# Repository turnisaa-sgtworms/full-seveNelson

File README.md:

my fun little keeb: 

designed to fit in a 60% case (minus two of the mounting points)

7u main cluster with a southy num pad and arrow keys/mini nav cluster

stm32 powered

built with the help of this guide: https://youtu.be/kGKN8SGkUD0?si=LNXGM9T6t6xvs4m5
by noah kiser

plate files are added, but will need updated when i fix the spacing :(

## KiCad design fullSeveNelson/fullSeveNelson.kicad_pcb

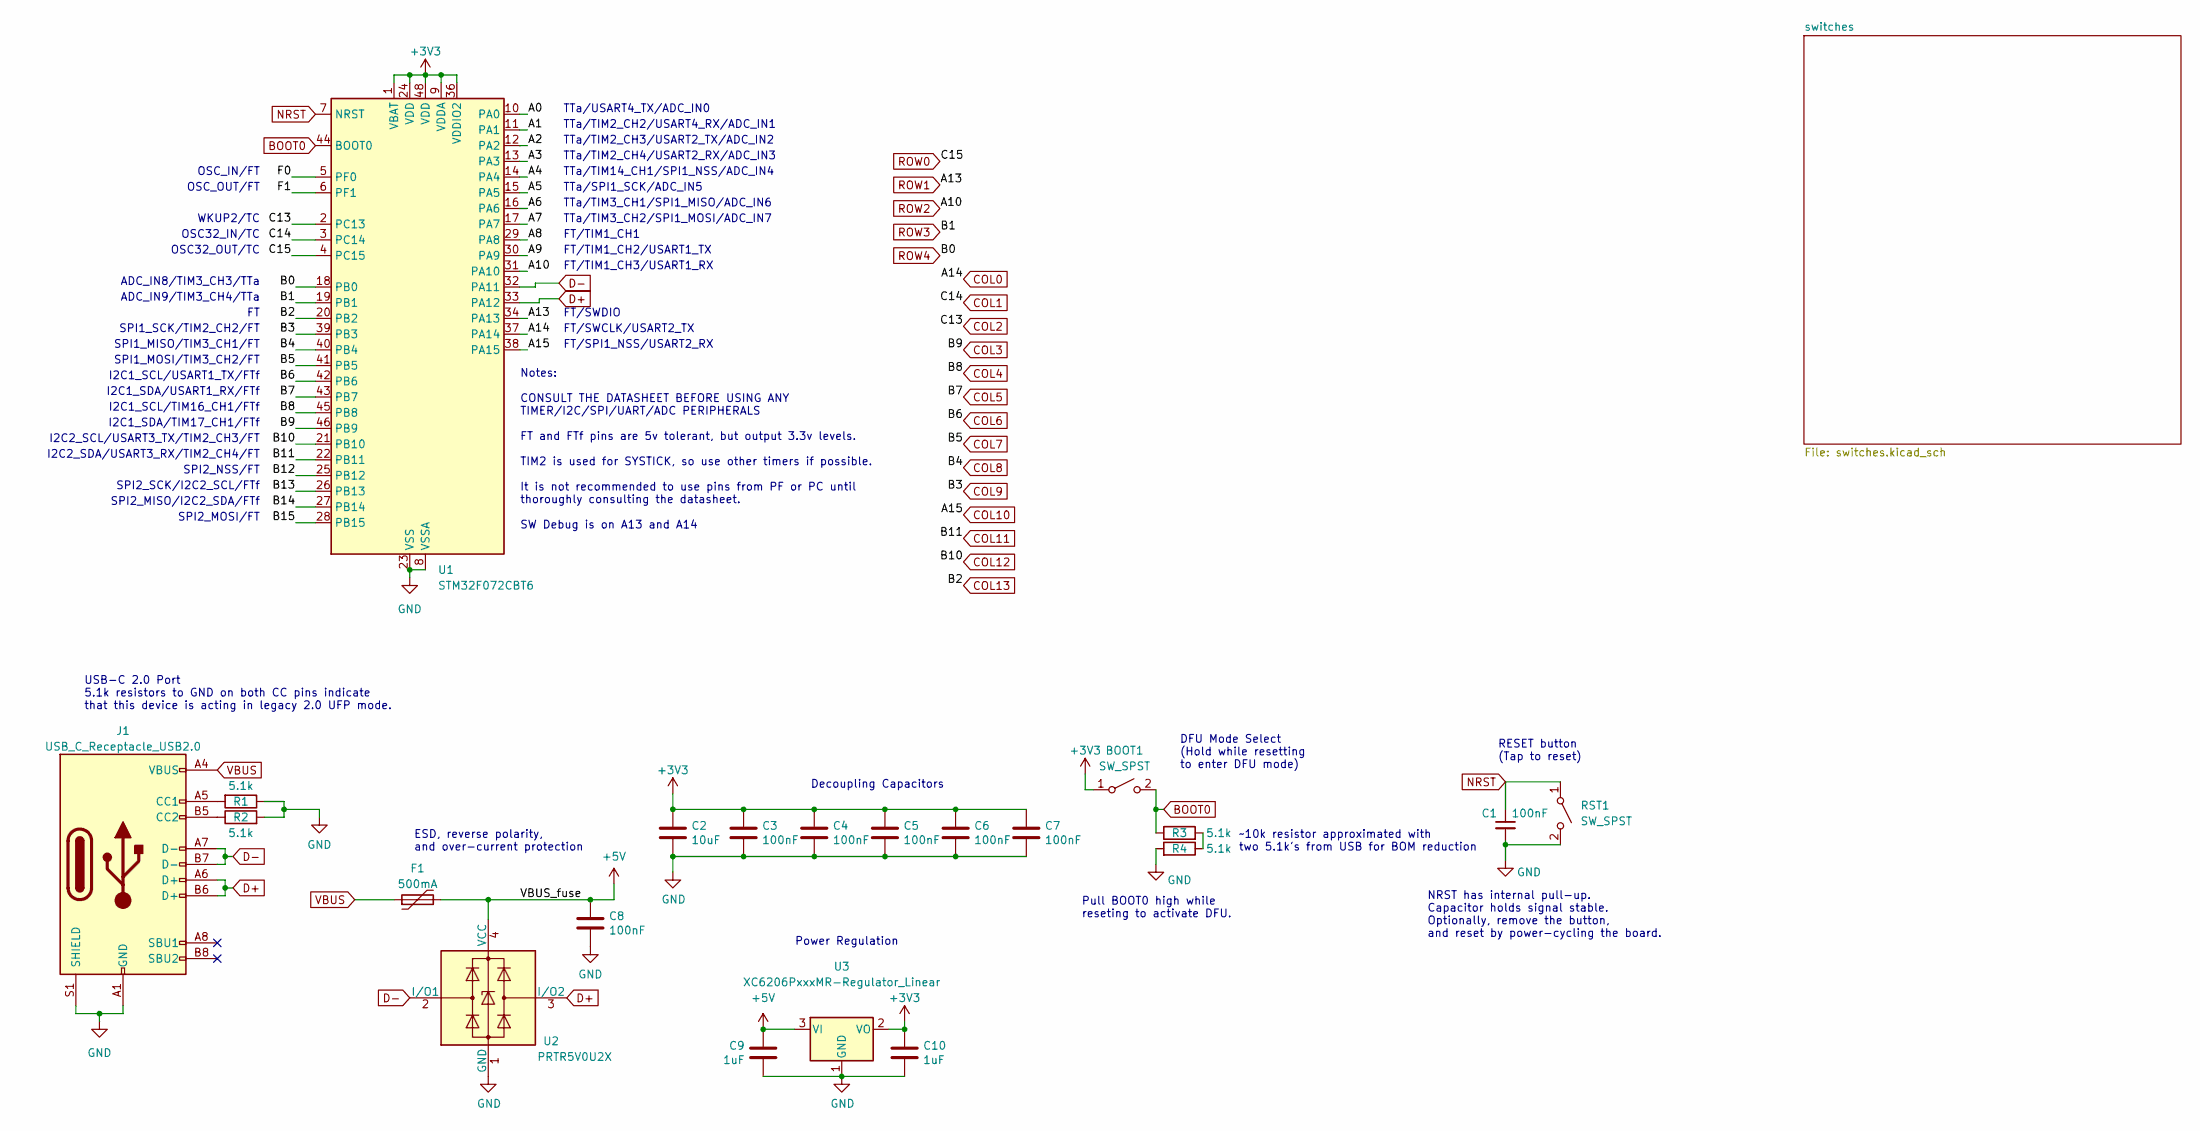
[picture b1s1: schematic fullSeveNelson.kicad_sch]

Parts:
BOOT1: SW_SPST; SW_SPST_TL3342
C1, C3, C4, C5, C6, C7, C8: 100nF; C_0402_1005Metric; LCSC C307331
C2: 10uF; C_0603_1608Metric; LCSC C307331
C9, C10: 1uF; C_0402_1005Metric; LCSC C307331
F1: 500mA; Fuse_1206_3216Metric; LCSC C135341
J1: USB_C_Receptacle_USB2.0; USB_C_Receptacle_HRO_TYPE-C-31-M-12; JlcRotOffset 180
R1, R2, R3, R4: 5.1k; R_0402_1005Metric
RST1: SW_SPST; SW_SPST_TL3342
U1: STM32F072CBT6; LQFP-48_7x7mm_P0.5mm; JlcRotOffset 90
U2: PRTR5V0U2X; SOT-143; LCSC C2827688
U3: XC6206PxxxMR-Regulator_Linear; SOT-23; LCSC C5446

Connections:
+3V3: BOOT1.1 (A), C2.1, C3.1, C4.1, C5.1, C6.1, C7.1, C10.1, U1.1 (VBAT), U1.9 (VDDA), U1.24 (VDD), U1.36 (VDDIO2), U1.48 (VDD), U3.2 (VO)
+5V: C8.1, C9.1, F1.2, U2.4 (VCC), U3.3 (VI)
/A0: U1.10 (PA0)
/A1: U1.11 (PA1)
/A2: U1.12 (PA2)
/A3: U1.13 (PA3)
/A4: U1.14 (PA4)
/A5: U1.15 (PA5)
/A6: U1.16 (PA6)
/A7: U1.17 (PA7)
/A8: U1.29 (PA8)
/A9: U1.30 (PA9)
/B12: U1.25 (PB12)
/B13: U1.26 (PB13)
/B14: U1.27 (PB14)
/B15: U1.28 (PB15)
/F0: U1.5 (PF0)
/F1: U1.6 (PF1)
BOOT0: BOOT1.2 (B), R3.1, U1.44 (BOOT0)
COL0: U1.37 (PA14); also elsewhere on the board
COL1: U1.3 (PC14); also elsewhere on the board
COL2: U1.2 (PC13); also elsewhere on the board
COL3: U1.46 (PB9); also elsewhere on the board
COL4: U1.45 (PB8); also elsewhere on the board
COL5: U1.43 (PB7); also elsewhere on the board
COL6: U1.42 (PB6); also elsewhere on the board
COL7: U1.41 (PB5); also elsewhere on the board
COL8: U1.40 (PB4); also elsewhere on the board
COL9: U1.39 (PB3); also elsewhere on the board
COL10: U1.38 (PA15); also elsewhere on the board
COL11: U1.22 (PB11); also elsewhere on the board
COL12: U1.21 (PB10); also elsewhere on the board
COL13: U1.20 (PB2); also elsewhere on the board
D+: J1.A6 (D+), J1.B6 (D+), U1.33 (PA12), U2.3 (I/O2)
D-: J1.A7 (D-), J1.B7 (D-), U1.32 (PA11), U2.2 (I/O1)
GND: C1.2, C2.2, C3.2, C4.2, C5.2, C6.2, C7.2, C8.2, C9.2, C10.2, J1.A1 (GND), J1.A12 (GND), J1.B1 (GND), J1.B12 (GND), J1.S1 (SHIELD), R1.1, R2.2, R4.2, RST1.2 (B), U1.8 (VSSA), U1.23 (VSS), U1.35 (VSS), U1.47 (VSS), U2.1 (GND), U3.1 (GND)
NRST: C1.1, RST1.1 (A), U1.7 (NRST)
unnamed: J1.A5 (CC1), R1.2
unnamed: J1.B5 (CC2), R2.1
unnamed: R3.2, R4.1
ROW0: U1.4 (PC15); also elsewhere on the board
ROW1: U1.34 (PA13); also elsewhere on the board
ROW2: U1.31 (PA10); also elsewhere on the board
ROW3: U1.19 (PB1); also elsewhere on the board
ROW4: U1.18 (PB0); also elsewhere on the board
VBUS: F1.1, J1.A4 (VBUS), J1.A9 (VBUS), J1.B4 (VBUS), J1.B9 (VBUS)

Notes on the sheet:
SPI1_SCK/TIM2_CH2/FT
FT/TIM1_CH1
FT/TIM1_CH3/USART1_RX
SPI2_NSS/FT
Notes: CONSULT THE DATASHEET BEFORE USING ANY TIMER/I2C/SPI/UART/ADC PERIPHERALS FT and FTf pins are 5v tolerant, but output 3.3v levels. TIM2 is used for SYSTICK, so use other timers if possible. It is not recommended to use pins from PF or PC until thoroughly consulting the datasheet. SW Debug is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
TTa/TIM2_CH4/USART2_RX/ADC_IN3
NRST has internal pull-up. Capacitor holds signal stable. Optionally, remove the button, and reset by power-cycling the board.
FT/SWDIO
Decoupling Capacitors
SPI1_MOSI/TIM3_CH2/FT
ADC_IN9/TIM3_CH4/TTa
I2C2_SCL/USART3_TX/TIM2_CH3/FT
SPI2_MISO/I2C2_SDA/FTf
FT/SWCLK/USART2_TX
I2C1_SCL/TIM16_CH1/FTf
~10k resistor approximated with two 5.1k's from USB for BOM reduction
TTa/TIM2_CH2/USART4_RX/ADC_IN1
USB-C 2.0 Port 5.1k resistors to GND on both CC pins indicate that this device is acting in legacy 2.0 UFP mode.
TTa/TIM2_CH3/USART2_TX/ADC_IN2
OSC_IN/FT
DFU Mode Select (Hold while resetting to enter DFU mode)
WKUP2/TC
I2C2_SDA/USART3_RX/TIM2_CH4/FT
ADC_IN8/TIM3_CH3/TTa
RESET button (Tap to reset)
Pull BOOT0 high while reseting to activate DFU.
I2C1_SDA/TIM17_CH1/FTf
TTa/SPI1_SCK/ADC_IN5
TTa/TIM3_CH1/SPI1_MISO/ADC_IN6
TTa/TIM3_CH2/SPI1_MOSI/ADC_IN7
OSC32_OUT/TC
FT/SPI1_NSS/USART2_RX
SPI1_MISO/TIM3_CH1/FT
OSC32_IN/TC
TTa/TIM14_CH1/SPI1_NSS/ADC_IN4
I2C1_SDA/USART1_RX/FTf
SPI2_MOSI/FT
FT/TIM1_CH2/USART1_TX
Power Regulation
SPI2_SCK/I2C2_SCL/FTf

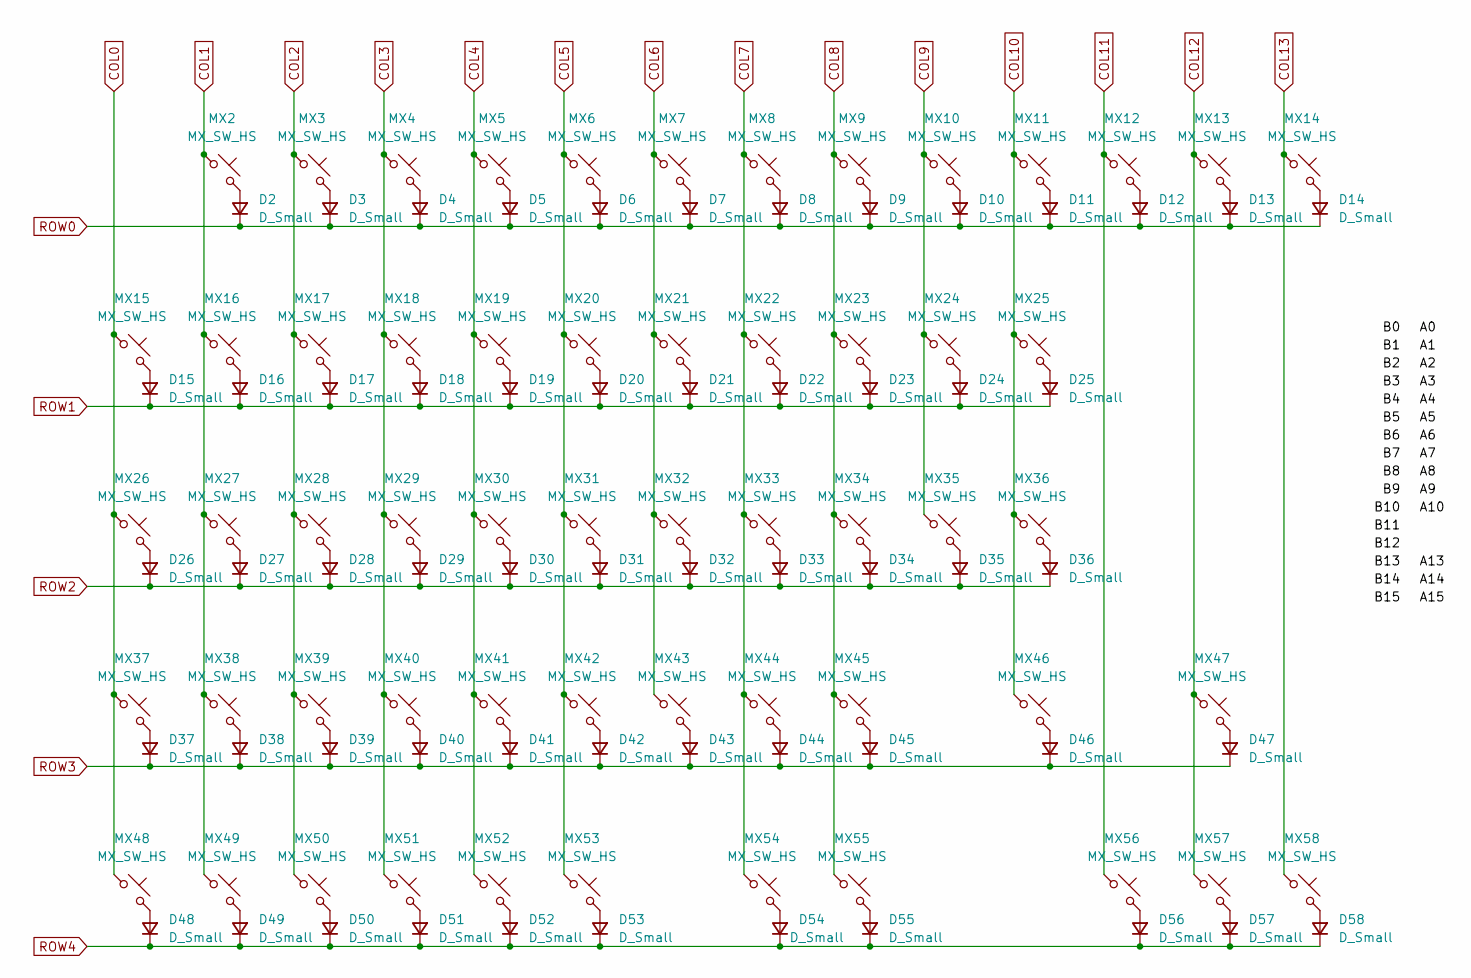
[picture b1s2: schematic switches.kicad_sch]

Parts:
D2, D3, D4, D5, D6, D7, D8, D9, D10, D11, D12, D13, D14, D15, D16, D17, D18, D19, D20, D21, D22, D23, D24, D25, D26, D27, D28, D29, D30, D31, D32, D33, D34, D35, D36, D37, D38, D39, D40, D41, D42, D43, D44, D45, D46, D47, D48, D49, D50, D51, D52, D53, D54, D55, D56, D57, D58: D_Small; D_SOD-123
MX2, MX3, MX4, MX5, MX6, MX7, MX8, MX9, MX10, MX11, MX12, MX13, MX14, MX15, MX16, MX17, MX18, MX19, MX20, MX21, MX22, MX23, MX24, MX25, MX26, MX27, MX28, MX29, MX30, MX31, MX32, MX33, MX34, MX35, MX36, MX37, MX38, MX39, MX40, MX41, MX42, MX43, MX44, MX45, MX46, MX47, MX48, MX49, MX50, MX51, MX52, MX53, MX54, MX55, MX56, MX57, MX58: MX_SW_HS; SW_MX_HS_CPG151101S11_1u

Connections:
COL0: MX15.1, MX26.1, MX37.1, MX48.1; also elsewhere on the board
COL1: MX2.1, MX16.1, MX27.1, MX38.1, MX49.1; also elsewhere on the board
COL2: MX3.1, MX17.1, MX28.1, MX39.1, MX50.1; also elsewhere on the board
COL3: MX4.1, MX18.1, MX29.1, MX40.1, MX51.1; also elsewhere on the board
COL4: MX5.1, MX19.1, MX30.1, MX41.1, MX52.1; also elsewhere on the board
COL5: MX6.1, MX20.1, MX31.1, MX42.1, MX53.1; also elsewhere on the board
COL6: MX7.1, MX21.1, MX32.1, MX43.1; also elsewhere on the board
COL7: MX8.1, MX22.1, MX33.1, MX44.1, MX54.1; also elsewhere on the board
COL8: MX9.1, MX23.1, MX34.1, MX45.1, MX55.1; also elsewhere on the board
COL9: MX10.1, MX24.1, MX35.1; also elsewhere on the board
COL10: MX11.1, MX25.1, MX36.1, MX46.1; also elsewhere on the board
COL11: MX12.1, MX56.1; also elsewhere on the board
COL12: MX13.1, MX47.1, MX57.1; also elsewhere on the board
COL13: MX14.1, MX58.1; also elsewhere on the board
unnamed: D2.2 (A), MX2.2
unnamed: D3.2 (A), MX3.2
unnamed: D4.2 (A), MX4.2
unnamed: D5.2 (A), MX5.2
unnamed: D6.2 (A), MX6.2
unnamed: D7.2 (A), MX7.2
unnamed: D8.2 (A), MX8.2
unnamed: D9.2 (A), MX9.2
unnamed: D10.2 (A), MX10.2
unnamed: D11.2 (A), MX11.2
unnamed: D12.2 (A), MX12.2
unnamed: D13.2 (A), MX13.2
unnamed: D14.2 (A), MX14.2
unnamed: D15.2 (A), MX15.2
unnamed: D16.2 (A), MX16.2
unnamed: D17.2 (A), MX17.2
unnamed: D18.2 (A), MX18.2
unnamed: D19.2 (A), MX19.2
unnamed: D20.2 (A), MX20.2
unnamed: D21.2 (A), MX21.2
unnamed: D22.2 (A), MX22.2
unnamed: D23.2 (A), MX23.2
unnamed: D24.2 (A), MX24.2
unnamed: D25.2 (A), MX25.2
unnamed: D26.2 (A), MX26.2
unnamed: D27.2 (A), MX27.2
unnamed: D28.2 (A), MX28.2
unnamed: D29.2 (A), MX29.2
unnamed: D30.2 (A), MX30.2
unnamed: D31.2 (A), MX31.2
unnamed: D32.2 (A), MX32.2
unnamed: D33.2 (A), MX33.2
unnamed: D34.2 (A), MX34.2
unnamed: D35.2 (A), MX35.2
unnamed: D36.2 (A), MX36.2
unnamed: D37.2 (A), MX37.2
unnamed: D38.2 (A), MX38.2
unnamed: D39.2 (A), MX39.2
unnamed: D40.2 (A), MX40.2
unnamed: D41.2 (A), MX41.2
unnamed: D42.2 (A), MX42.2
unnamed: D43.2 (A), MX43.2
unnamed: D44.2 (A), MX44.2
unnamed: D45.2 (A), MX45.2
unnamed: D46.2 (A), MX46.2
unnamed: D47.2 (A), MX47.2
unnamed: D48.2 (A), MX48.2
unnamed: D49.2 (A), MX49.2
unnamed: D50.2 (A), MX50.2
unnamed: D51.2 (A), MX51.2
unnamed: D52.2 (A), MX52.2
unnamed: D53.2 (A), MX53.2
unnamed: D54.2 (A), MX54.2
unnamed: D55.2 (A), MX55.2
unnamed: D56.2 (A), MX56.2
unnamed: D57.2 (A), MX57.2
unnamed: D58.2 (A), MX58.2
ROW0: D2.1 (K), D3.1 (K), D4.1 (K), D5.1 (K), D6.1 (K), D7.1 (K), D8.1 (K), D9.1 (K), D10.1 (K), D11.1 (K), D12.1 (K), D13.1 (K), D14.1 (K); also elsewhere on the board
ROW1: D15.1 (K), D16.1 (K), D17.1 (K), D18.1 (K), D19.1 (K), D20.1 (K), D21.1 (K), D22.1 (K), D23.1 (K), D24.1 (K), D25.1 (K); also elsewhere on the board
ROW2: D26.1 (K), D27.1 (K), D28.1 (K), D29.1 (K), D30.1 (K), D31.1 (K), D32.1 (K), D33.1 (K), D34.1 (K), D35.1 (K), D36.1 (K); also elsewhere on the board
ROW3: D37.1 (K), D38.1 (K), D39.1 (K), D40.1 (K), D41.1 (K), D42.1 (K), D43.1 (K), D44.1 (K), D45.1 (K), D46.1 (K), D47.1 (K); also elsewhere on the board
ROW4: D48.1 (K), D49.1 (K), D50.1 (K), D51.1 (K), D52.1 (K), D53.1 (K), D54.1 (K), D55.1 (K), D56.1 (K), D57.1 (K), D58.1 (K); also elsewhere on the board

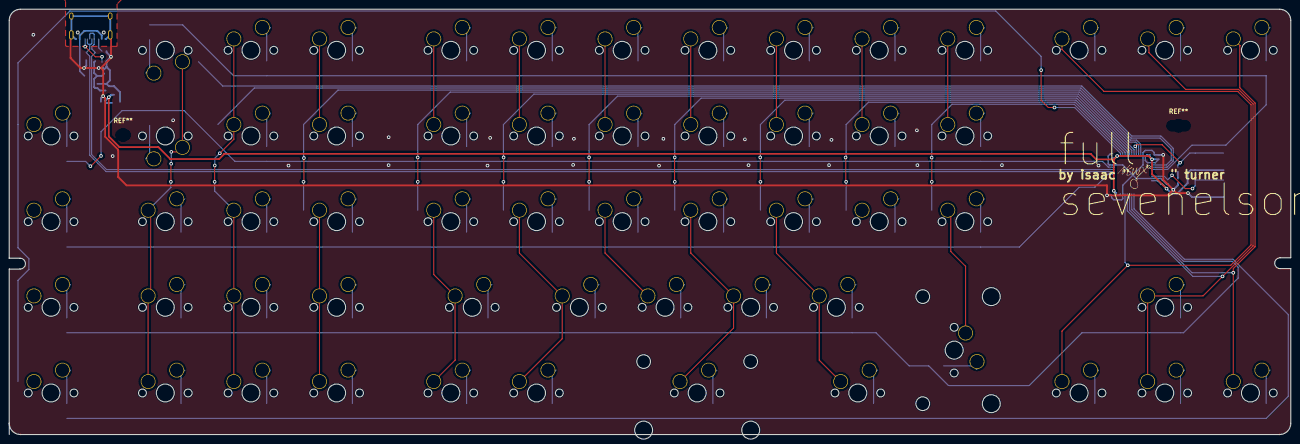
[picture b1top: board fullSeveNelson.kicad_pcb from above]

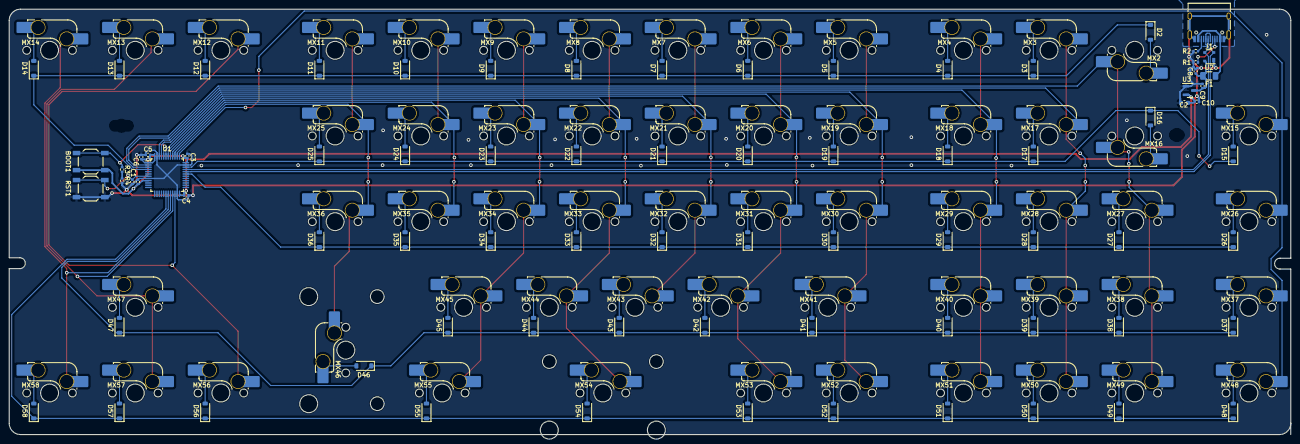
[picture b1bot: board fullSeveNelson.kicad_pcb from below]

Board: 2 copper layers, 285.0 x 94.6 mm, 135 parts (135 on the bottom side), 87 nets.

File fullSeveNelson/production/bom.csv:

Designator,Footprint,Quantity,Value,LCSC Part #
,,1,,
"BOOT1, RST1",SW_SPST_TL3342,2,SW_SPST,
"C1, C3, C4, C5, C6, C7, C8",0402,7,100nF,C307331
"C10, C9",0402,2,1uF,C307331
C2,0603,1,10uF,C307331
"D10, D11, D12, D13, D14, D15, D16, D17, D18, D19, D2, D20, D21, D22, D23, D24, D25, D26, D27, D28, D29, D3, D30, D31, D32, D33, D34, D35, D36, D37, D38, D39, D4, D40, D41, D42, D43, D44, D45, D46, D47, D48, D49, D5, D50, D51, D52, D53, D54, D55, D56, D57, D58, D6, D7, D8, D9",D_SOD-123,57,D_Small,
F1,1206,1,500mA,C135341
J1,USB_C_Receptacle_HRO_TYPE-C-31-M-12,1,USB_C_Receptacle_USB2.0,
"MX10, MX11, MX12, MX13, MX14, MX15, MX16, MX17, MX18, MX19, MX2, MX20, MX21, MX22, MX23, MX24, MX25, MX26, MX27, MX28, MX29, MX3, MX30, MX31, MX32, MX33, MX34, MX35, MX36, MX37, MX38, MX39, MX4, MX40, MX41, MX42, MX43, MX44, MX45, MX46, MX47, MX48, MX49, MX5, MX50, MX51, MX52, MX53, MX54, MX55, MX56, MX57, MX58, MX6, MX7, MX8, MX9",SW_MX_HS_CPG151101S11_1u,57,MX_SW_HS,
"R1, R2, R3, R4",0402,4,5.1k,
U1,LQFP-48_7x7mm_P0.5mm,1,STM32F072CBT6,
U2,SOT-143,1,PRTR5V0U2X,C2827688
U3,SOT-23,1,XC6206PxxxMR-Regulator_Linear,C5446

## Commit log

2025-03-05 created repo 😎
2025-03-05 made fullSeveNelson
2025-03-05 updated fills
2025-03-05 fixed footprints
2025-03-05 more swag business
2025-03-05 plate files
2025-03-05 added json for better seperated layout
2025-03-06 fixed spacing and mounting holes
2025-03-06 fixed plate for new spacing
